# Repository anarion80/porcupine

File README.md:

# Porcupine 

Porcupine is an autogenerated, ergonomic, split, 36-42 key, wired/wireless, columnar-staggered keyboard. It is designed to fit my needs and my hand, but it can be easily updated thanks to declarative design.
It uses a ProMicro-compatible MCU board and supports both [QMK](https://qmk.fm/) and [ZMK](https://zmk.dev/) firmwares.

It is inspired by:

* [[Ferris] Sweep](https://github.com/davidphilipbarr/Sweep) keyboard
* [rae-dux](https://github.com/andrewjrae/rae-dux) keyboard
* [samoklava](https://github.com/soundmonster/samoklava) and its workflow
* all the work done by [Ben Vallack](https://github.com/benvallack) on his [Youtube channel](https://www.youtube.com/c/BenVallack)

It is fully Open-Source: the KiCad files are released under the solderpad license, version 2.1. The software (scripts/config files) in this repository is released under the GPL.

## :sparkles: Features

* Autogenerated - PCB layout is declared using YAML config files and generated into PCB files using [Ergogen](https://github.com/ergogen/ergogen) tool (migrated to V4).
Use [my fork](https://github.com/anarion80/ergogen) of it for added footprints.
* 3 variants:
  * regular 5x3 column-staggered ortholiner layout with 3 thumb keys (36 keys total)
  * regular 5x3 column-staggered ortholiner layout with 4 thumb keys (38 keys total)
  * regular 6x3 column-staggered ortholiner layout with 4 thumb keys (42 keys total)
* Wired or wireless
* Low-profile (using [Kailh Choc](http://www.kailh.com/en/Products/Ks/CS/) switches)
* Reversible PCB (save cost in production)
* Pro-micro/Elite C/Proton C/[nice!nano](https://nicekeyboards.com/nice-nano/) support
* Hot-Swap support
* SplitKB Tenting puck support.
* uses [KiKit](https://github.com/yaqwsx/KiKit) to render PCB previews (see below)
* uses [KiBot](https://github.com/INTI-CMNB/KiBot) to run DRC, create Gerber and Drill files for production (and Interactive BOM and 3d renders just for fun)

Front/Left | Back/Right
-|-
Porcupine
 | 
Porcupine 4 thumb keys
 | 
Porcupine 3x6
 | 
Prototype boards (generated using Ergogen v3 still):
 | 
Porcupine working final prototype

## :receipt: Components list

To build and use a Porcupine you will need:

* 1x PCB Kit
* 2x promicro compatible boards or 2 nice!nanos.
* 34-42 Choc V1 Low profile switches
* 34-42 Kailh Choc hot-swap sockets
* 34-42 diodes (SMD or THT)
* 34-42 keycaps
* 2x reset switches (optional; B3U-1000P(M))
* 4x 12x low profile female headers (optional; only if you want the microcontroller socketed)
* 48x Mill Max low profile socket pins (optional; socketed microcontroller; if you are using tht diodes you can use the legs of those diodes)
* Some little rubber feet/bumpers
* 2x power (On/Off) switches (optional; MSK 12C02)
* JST PH battery connector (wireless build; S2B-PH-K)
* Li-Po 110mAh battery (wireless build; 301230)
* 1x TRRS (not TRS!) cable (wired build only)
* 2x TRRS Jack [PJ-320A] (wired build only)
* 1 USB Cable (wired build; depends on your micro-controller choice)

## :construction_worker: Build Guide

Manually-routed PCBs for each variant are included in the `output` folder, so if they are fine for you, you can just take them directly, have them produced and then build.

For step-by-step instructions on assembling the keyboard, see the [Porcupine build guide](build_guide.md).

## :keyboard: Firmware/keymaps

[QMK firmware and keymaps](https://github.com/anarion80/porcupine_qmk) - confirmed working with the prototype boards! :tada:

[ZMK firmware and keymaps](https://github.com/anarion80/zmk-config-porcupine) - confirmed working now as well! :tada:

## :pencil2: How to use/update/modify

If you would like to modify this:

* fork it
* (optionally, to see the 3d view of generated PCB in KiCad)
  * copy 3d models from `3dmodels/ergogen` folder into your KiCad's installation `${KICAD6_3RD_PARTY}/3dmodels/ergogen/` folder[^1].
* change `input/porcupine*.yaml` to your liking
* commit to Github

The associated Github Workflow action will then generate the PCB, 2D Images of the board and a whole KiBot package with Gerber/Drill files, Interactive Bom, images and renders.
The files will be available as Workflow Action artifacts.

:warning: The boards will come out unrouted! But if you add a manually routed board to `output/[board_name]/pcbs/` folder, the Workflow will pick it up and generate everything for it as well.

If you would rather do all that locally, then:

* install Ergogen: `npm install`
* install Docker
* generate PCBs: `npm run gen_pcb`
* generate images: `npm run gen_images`
* generate Kibot package: `npm run gen_kibot`

Further:

* route the board manually in KiCad
* produce (for eample in [JLCPCB](https://jlcpcb.com/) or [PCBWay](https://www.pcbway.com/))
* build
* load firmware
* use it!

## :warning: Important Notes

* Kicad files are 6.0, so unfortunately not backwards compatible.
* If you're going for wired version or just want to skip out on the power switch, you need to solder the Jumper.
* Manually-routed boards are included, but there is no autorouting for generated boards.
* You need to have Docker installed to use `npm run gen_images` or `npm run gen_kibot` to generate pcb images and Kibot bundle.

## :hammer: TODO

* [ ] a variant with MX switches
* [x] automation of DRC/BOM/Gerber creation/validation with Github workflow
* [ ] proper 3d-printable cases
* [ ] LED support

## :page_facing_up: Disclaimer

The author(s) waive(s) responsibility for any damage or regulatory violations caused by using this hardware and software (see license). Please consult your local regulations around radio frequencies and what's allowed for DIY projects in your country.

Porcupine logo by [@migorzka](https://www.instagram.com/migorzka/)

[^1]: The models are bundled here in the repository, but they are taken from [KiCad](https://www.kicad.org/) directly, from [keyswitch-kicad-library](https://github.com/perigoso/keyswitch-kicad-library) or are created by me.

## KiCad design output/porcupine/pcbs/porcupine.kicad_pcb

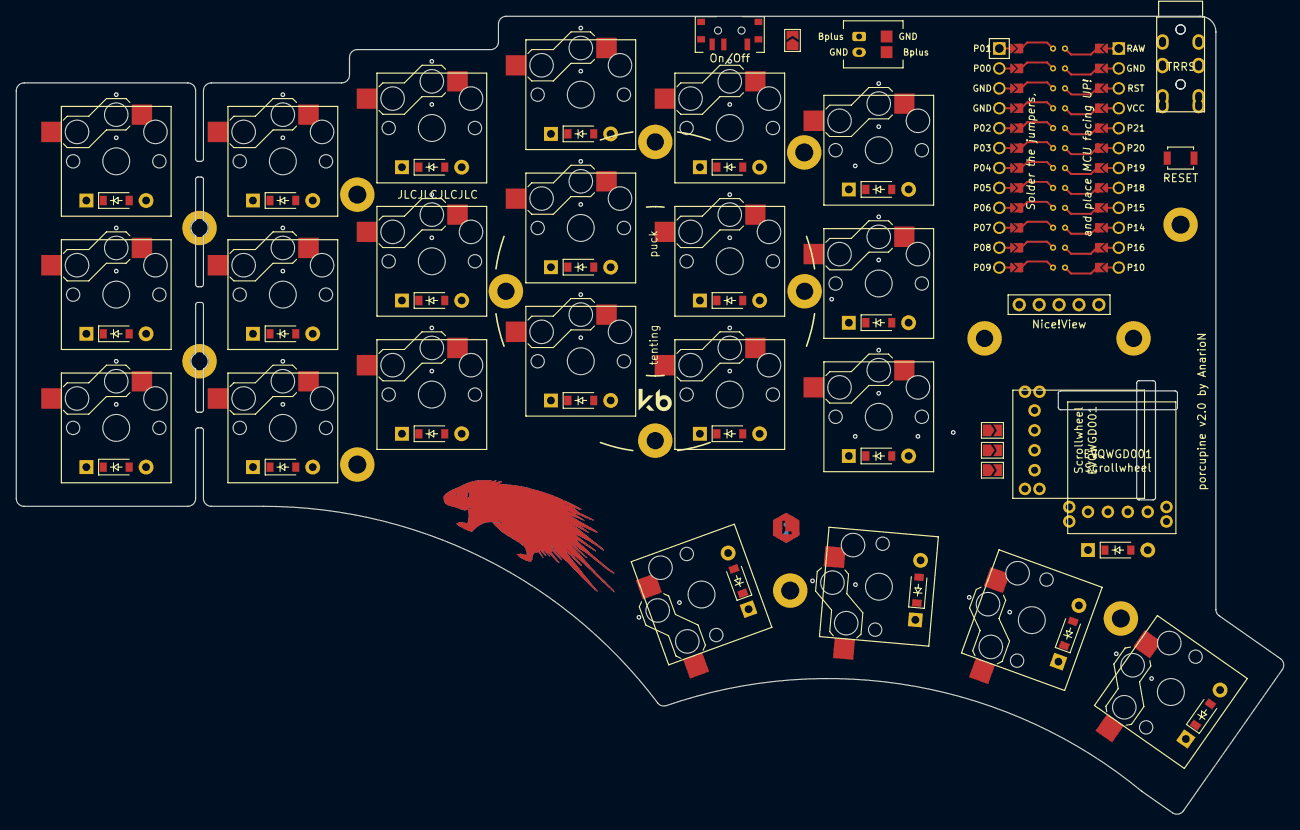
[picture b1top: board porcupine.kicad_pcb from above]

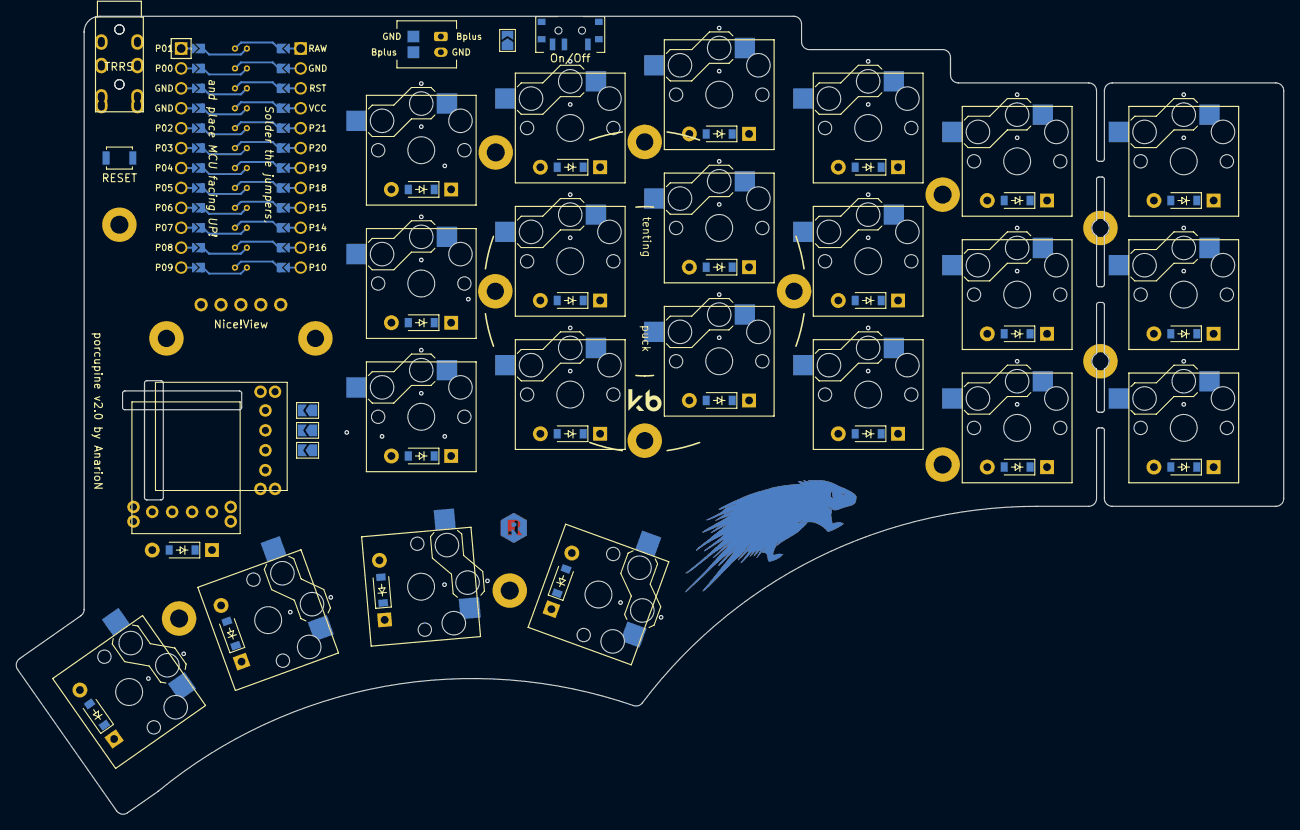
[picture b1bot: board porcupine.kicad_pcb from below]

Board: 2 copper layers, 161.7 x 101.8 mm, 80 parts (8 on the bottom side), 48 nets, no tracks yet.

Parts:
BAT1: bat2p0
D1, D2, D3, D4, D5, D6, D7, D8, D9, D10, D11, D12, D13, D14, D15, D16, D17, D18, D19, D20, D21, D22, D23: D_SOD-123; SOD-123
H1, H2, H3, H4, H5, H6, H7, H8, H9, H10: hole; Through Hole
J1, J2, J3, J4, J5, J6, J7, J8: Jumper; SolderJumper-2_P1.3mm_Open_TrianglePad1.0x1.5mm
LOGO_B: Porcupine Logo
LOGO_F: Porcupine Logo
MCU1: ProMicro
Nice!View1: niceview_headers
PAD1, PAD2: SMDPad
RST1_B, RST1_F: SW_Push; SW_SPST_B3U-1000P
S1, S2, S3, S4, S5, S6, S7, S8, S9, S10, S11, S12, S13, S14, S15, S16, S17, S18, S19, S20, S21, S22: PG1350
S23, S24: RollerEncoder_Panasonic_EVQWGD001
SW1: SW_SPDT_PCM12
Side_B: Side Indicator
Side_F: Side Indicator
TP1: Tenting Puck
TRRS_B: AudioJack4; TRRS-PJ-320A-dual
TRRS_F: AudioJack4; TRRS-PJ-320A-dual

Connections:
Bplus: BAT1.1, J7.1, J8.1, PAD1.1, SW1.2
CS: MCU1.24, Nice!View1.1
ENCA: J3.1, J6.1, MCU1.6
ENCA_GND: J3.2, J5.2, S23.C, S24.C
ENCB: J1.1, J4.1, MCU1.5
ENCB_undef: J1.2, S23.A, S24.A
GND: BAT1.2, J2.1, J5.1, MCU1.2, MCU1.21, MCU1.22, Nice!View1.1, PAD2.1, RST1_B.2, TRRS_B.R1
GND_ENCA: J2.2, J6.2, S23.B, S24.B
RAW: J7.2, J8.2, MCU1.1, SW1.1
RST: MCU1.3, RST1_B.1
SCL: MCU1.19, Nice!View1.3
SDA: MCU1.20, Nice!View1.4
VCC: MCU1.4, Nice!View1.2, TRRS_B.S, TRRS_B.T
col_index: MCU1.11, S13.2, S14.2, S15.2, S21.2
col_inner: MCU1.12, S16.2, S17.2, S18.2, S22.2, S23.S1, S24.S1
col_middle: MCU1.10, S10.2, S11.2, S12.2, S20.2
col_outer: MCU1.7, S1.2, S2.2, S3.2
col_pinky: MCU1.8, S4.2, S5.2, S6.2
col_ring: MCU1.9, S7.2, S8.2, S9.2, S19.2
far_thumb: D22.1, D22.2, S22.1
home_thumb: D21.1, D21.2, S21.1
index_bottom: D13.1, D13.2, S13.1
index_home: D14.1, D14.2, S14.1
index_top: D15.1, D15.2, S15.1
inner_bottom: D16.1, D16.2, S16.1
inner_home: D17.1, D17.2, S17.1
inner_thumb: D19.1, D19.2, S19.1
inner_top: D18.1, D18.2, S18.1
middle_bottom: D10.1, D10.2, S10.1
middle_home: D11.1, D11.2, S11.1
middle_top: D12.1, D12.2, S12.1
near_thumb: D20.1, D20.2, S20.1
outer_bottom: D1.1, D1.2, S1.1
outer_home: D2.1, D2.2, S2.1
outer_top: D3.1, D3.2, S3.1
pinky_bottom: D4.1, D4.2, S4.1
pinky_home: D5.1, D5.2, S5.1
pinky_top: D6.1, D6.2, S6.1
ring_bottom: D7.1, D7.2, S7.1
ring_home: D8.1, D8.2, S8.1
ring_top: D9.1, D9.2, S9.1
row_bottom: D1.1, D1.2, D4.1, D4.2, D7.1, D7.2, D10.1, D10.2, D13.1, D13.2, D16.1, D16.2, MCU1.16
row_home: D2.1, D2.2, D5.1, D5.2, D8.1, D8.2, D11.1, D11.2, D14.1, D14.2, D17.1, D17.2, MCU1.17
row_thumb: D19.1, D19.2, D20.1, D20.2, D21.1, D21.2, D22.1, D22.2, D23.1, D23.2, MCU1.15
row_top: D3.1, D3.2, D6.1, D6.2, D9.1, D9.2, D12.1, D12.2, D15.1, D15.2, D18.1, D18.2, MCU1.18
scrollwheel_scrollwheel: D23.1, D23.2, S23.S2, S24.S2
trrs: MCU1.23, TRRS_B.R2
undef_ENCB: J4.2, S23.D, S24.D

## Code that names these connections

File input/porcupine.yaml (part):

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        pinky:
          key:
            spread: choc1u/2 + choc125u/2 + 1.5
            column_net: col_pinky
        ring:
          key:
            stagger: ky/4
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          P21: ENCB
          P20: ENCA
          P19: col_outer
          P18: col_pinky
          P15: col_ring
          P14: col_middle
          P16: col_index
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          ref: matrix_pinky_top
          shift: [0,3]
        params:
          net: col_pinky
      via_pinky_top:
        what: simple_via
        adjust:
          ref: matrix_pinky_top
          shift: [0,8.5]
        params:
          net: pinky_top
      via_col_pinky_2:
        what: simple_via
        adjust:
          ref: matrix_pinky_home
          shift: [0,3]
        params:
          net: col_pinky
      via_pinky_home:
        what: simple_via
        adjust:
          ref: matrix_pinky_home
          shift: [0,8.5]
        params:
          net: pinky_home
      via_col_pinky_3:
        what: simple_via
        adjust:
          ref: matrix_pinky_bottom
          shift: [0,3]
        params:
          net: col_pinky
      via_pinky_bottom:
        what: simple_via
        adjust:
          ref: matrix_pinky_bottom
          shift: [0,8.5]
        params:
          net: pinky_bottom
      via_col_ring_1:
        what: simple_via
        adjust:
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
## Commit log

2023-01-22 Update input and add manually routed boards
2023-01-22 Update scripts permissions on github
2023-01-25 Update 6x3 variant
    * Removed unnecessary P19 via
    * Fix outer column stagger
    * Fix P19 matrix ring bottom via
    * Resized GND zones
2023-01-25 Add new logo
2023-01-26 Update workflow
2023-02-28 ✏️ Fix typo in README
2023-03-12 🚨 Fix markdown lint in README
2023-03-12 🚧 Added pictures of prototype boards
2023-03-12 🚧 Added link to QMK firmware/keymaps
2023-05-13 🚀 Confirmed working with QMK
2023-07-04 Remove pinky stagger
2023-07-04 Reorganize controller area
2023-07-04 Update side indicator and info text
2023-07-04 Update porcupine logo
2023-07-05 Add 1.5u keycaps to outer column
2023-07-05 Move the mounting holes
2023-07-06 Vias and mounting holes
2023-07-06 Fix missing thumb keys outlines
2023-07-06 Add a break-away part
2023-07-06 Move info
2023-07-06 Move mounting holes to footprints
2023-07-06 Move side indicator
2023-07-06 More room for battery header
2023-08-19 :sparkles: Added ZMK config
2023-09-08 ✨ Added ZMK config
2023-09-09 Update README to reference Kicad 7
2023-09-12 Big update - added scrollwheel and nice!view
    * Added scrollwheel
    * Added nice_view
    * Moved components around for better spacing
    * Move columns and rows to a new set of pins for easier routing
    * Rename promicro pins to easier see pins for I2C/Scrollwheel
2023-09-12 🔥 Remove old versions
2023-09-12 ⬆️ Update ergogen link
2023-09-12 📝 Update README
2023-09-12 ⚰️ Remove reference to old 6x3
2023-09-12 ⬆️ Update ergogen dependency
2023-09-15 ♻️ Update to have proper tag usage in 'where' keys
2023-09-15 ♻️ Further anchor and ref cleanup
2023-09-16 Add one more mounting hole on the inside
2023-09-17 ♻️ Redesigned the thumb fan
2023-09-18 Update Kibot for Kicad7
2023-09-18 Add Encoder 3dmodel
2023-09-18 Change outer column to 1.25u
2023-09-18 Expand the top plate
2023-09-27 Redesigned thumb fan again
2023-09-27 Update Kibot
2023-09-28 Update gen_images to only consider kicad pcb files
2023-09-28 Align vias
2023-09-28 Make the PCB rounder
2023-09-28 Bring back logo
2023-09-28 Add break-away part to top plate
2023-09-28 Move the bottom right screw down
2023-09-28 Add images and cases
2023-09-28 🗑️ Outlines clean-up
2023-09-28 Add both horizontal and vertical scrollbar
2023-09-29 Align battery pads
2023-09-30 Update outlines for 3d printed case
2023-10-14 Make name and version a reference
2024-08-13 👷 Added a build guide

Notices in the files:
README.md:
License: SHL-2.1
License: GPL
